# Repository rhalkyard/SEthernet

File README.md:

# SEthernet and SEthernet/30

Modern, low-cost 10/100 Ethernet for the Macintosh SE and SE/30.

## Introduction

It's an unfortunate reality of retrocomputing that, as time goes on, original
hardware only ever becomes more scarce, and usually more expensive.

While PDS ethernet cards are certainly not _scarce_ yet, the collector appeal of
Compact Macs means that cards are in high demand, with consequent high prices.
As of this writing (October 2023), the going eBay rate for them seems to be of
the order of $US 150-200, which is a bit steep for those of us who remember
finding them in electronics-recycler dollar bins.

While other projects have aimed to clone these original cards, such an approach
comes with a downside - the ethernet controller chips used in them have been out
of production for many years, and the controllers and (even more so) their
supporting components, are difficult to find.

While cloned cards trade off parts sourcing difficutly (and cost) for the
significant advantage of being able to use existing drivers, this project takes
the opposite approach: design an all-new card using a modern, readily-available
ethernet controller, and write a new driver for it. How hard can it be?
[^howhard]

## Hardware Overview

Both the SEthernet and SEthernet/30 use the Microchip
[ENC624J600](https://ww1.microchip.com/downloads/aemDocuments/documents/OTH/ProductDocuments/DataSheets/39935c.pdf)
all-in-one embedded ethernet controller. It's cheap, readily available, has a
straightforward software interface without too many glaring misfeatures (I'm
looking at you, RTL8019AS), and amongst its multitude of configurable host-bus
modes, it has one that matches the 68k processor bus nicely.

Since the Macintosh SE lacks any real infrastructure for expansion beyond
"here's a connector with the CPU bus on it," the SEthernet board is a very dumb
device. It simply maps the ENC624J600 into a vacant chunk of memory at `0x80
0000`-`0x80 ffff` and connects it to an interrupt line. Hardware detection,
interrupt vector interception, and device configuration are all left to the
driver to implement.

The Macintosh SE/30 is a more civilised machine, and the SEthernet/30 provides a
[declaration ROM](rom/se30) and multiple addressing options (configurable by
jumper) to take full advantage of the Slot Manager and coexist with multiple PDS
cards. Potentially, the driver could even be built into the declaration ROM,
allowing for a truly plug-and-play solution. To facilitate driver updates, the
declaration ROM is a flash chip, with logic to allow for in-system programming.

## Current project status

### Hardware

Hardware Revision 1 is largely 'done', and corrects the numerous issues of my
initial "Revision 0" boards. A few mechanical tweaks remain to get mounting
holes in exactly the right spot, and relocate connectors for easier access.

### Software

The core driver is functional and stable enough for everyday use. Real-world
performance is marginally better than a comparable vintage card, but there is
likely room to improve - especially in the rather convoluted receive routine.

Support for promiscuous mode, and the `ERead` call are not yet implemented.

The installer has some rough edges (no hardware detection or driver version
detection on the SE), but functions as a way to get drivers onto a system.

The SE/30 board's Declaration ROM must be programmed before the card can be
recognized. This can be done in-system using the
[programROM](software/tools/programROM/) application provided on the installer
disk, but right now this is a very ugly and user-unfriendly console application,
and really should be turned into a proper GUI app.

Testing has been done on my unmodified SE and SE/30 under Systems 6.0.8, 7.1,
and 7.5.5.

A driver for A/UX 2 and 3 can be found at
https://github.com/rhalkyard/SEthernet-AUX. 

## Project files

Schematics: [SEthernet](boards/se/se.pdf) -
[SEthernet/30](boards/se30/se30.pdf) - [Breakout Board](boards/breakout/breakout.pdf)

Glue Logic: [SEthernet](pld/se) - [SEthernet/30](pld/se30)

[SEthernet30 Declaration ROM](rom/se30)

[Driver](software/driver)

## Required tools

### Schematics, board layout and BOM

[KiCad 7](https://www.kicad.org/)

### Programmable Logic

[WinCUPL and ATMISP](https://www.microchip.com/en-us/products/fpgas-and-plds/spld-cplds/pld-design-resources)
(see [`pld/README.md`](pld/README.md) for notes on WinCUPL)

### Declaration ROM, driver and software

- [Retro68](https://github.com/autc04/Retro68) built with [Apple Universal
  Interfaces](https://github.com/autc04/Retro68#apple-universal-interfaces-vs-multiversal-interfaces)
  (at the time of writing, the default free-software Multiversal Interfaces do
  not include some necessary headers)

- [CMake](https://cmake.org/)

- [Python 3](https://www.python.org)

### Installer

- [hfsutils](https://www.mars.org/home/rob/proj/hfs/)

- [Python 3](https://www.python.org)

- [Mini vMac](https://www.gryphel.com/c/minivmac/index.html)

## License

The hardware components of this project ([board designs](boards/) and
[programmable logic](pld/)) are licensed under the [Strongly-Reciprocal CERN
Open Hardware License, version 2](CERN-OHL-S-2.0).

The [software components](software/) of this project are licensed under the [GNU
General Public License v3.0](COPYING).

While my choice to make this project open-source is very much a deliberate one,
I have a few further requests, on the basis of "I can't and won't enforce these,
but I'd appreciate if you respected them." It's unfortunate that I have to
mention this, but given how a few recent projects in the retro-hardware
community have splintered, I feel that it's necessary to say:

- Please don't sell cards commercially/for profit without checking with me
  first. I have plans for a sales and manufacturing partnership that will sell
  boards affordably, with full support. I don't mind if you order a batch of
  boards for yourself and sell the extras on a break-even basis, but please make
  it clear that these are not 'official' SEthernet products.

- Please contribute back, rather than simply forking the project. I strongly
  encourage people to modify the design, adapt it to other systems, integrate it
  into other devices. But unless what you're working on is a radical departure
  from the basic SEthernet design, I'd much rather see a unified, collaborative
  effort that is supported by a single software stack, rather than having it be
  fragmented.

If you have any questions, feel free to reach out to me, I don't bite!

## Useful reference material

- [ENC624J600 datasheet](https://ww1.microchip.com/downloads/aemDocuments/documents/OTH/ProductDocuments/DataSheets/39935c.pdf)

- [Designing Cards and Drivers for the Macintosh Family (3rd
  Edition)](https://www.vintageapple.org/inside_o/pdf/Designing_Cards_and_Drivers_for_the_Macintosh_Family_3rd_Edition_1992.pdf)

- [Inside Macintosh (1994): Networking](https://www.vintageapple.org/inside_r/pdf/Networking_1994.pdf)

- [Inside Macintosh (1994): Devices](https://www.vintageapple.org/inside_r/pdf/Devices_1994.pdf)

- [Glenn Anderson's ethernet driver page](https://www.mactcp.net/ethernet.html) -
  contains C source for a DP8390-based card.

- [Mac Driver Museum: Network
  Drivers](https://vintageapple.org/macdrivers/network.shtml) - good material
  for reverse-engineering. In particular, the Dayna ethernet drivers contain
  debug symbols, which are quite handy for our purposes.

- [Rob Braun's declaration ROM page](http://www.synack.net/~bbraun/declrom.html)
  has useful information about declaration ROMs and how they work.

[^howhard]: [Arrested Development narrator voice]: It was, in fact, quite hard

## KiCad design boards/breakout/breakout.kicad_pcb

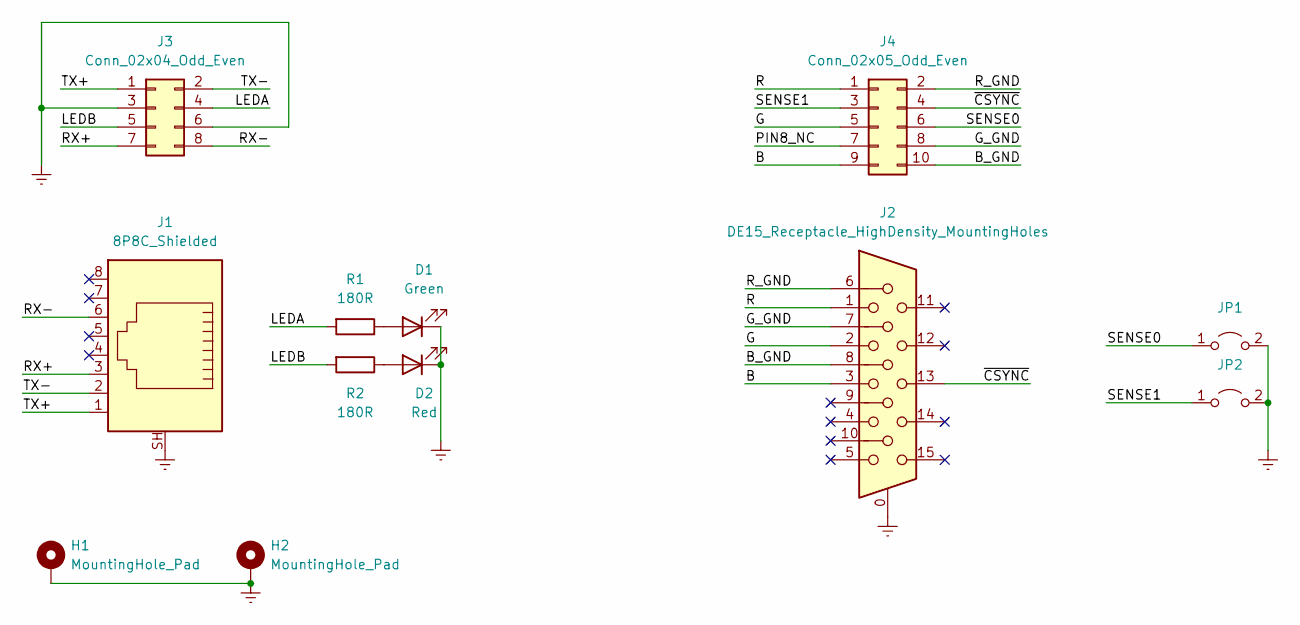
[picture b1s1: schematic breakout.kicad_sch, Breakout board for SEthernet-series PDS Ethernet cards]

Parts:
D1: Green; LED_D3.0mm; Digikey 151031VS06000
D2: Red; LED_D3.0mm; Digikey 151031SS06000
H1, H2: MountingHole_Pad; Wurth_9774025360R; Digikey 9774025360R
J1: 8P8C_Shielded; Kycon-GDTX-S-88_Vertical; Digikey GDTX-S-88
J2: DE15_Receptacle_HighDensity_MountingHoles; DSUB-15-HD_Female_Vertical_P2.29x1.98mm_MountingHoles; Digikey L77HDEH15SOL2RM832
J3: Conn_02x04_Odd_Even; IDC-Header_2x04_P2.54mm_Vertical; Digikey 302-S101
J4: Conn_02x05_Odd_Even; IDC-Header_2x05_P2.54mm_Vertical; Digikey 302-S101
JP1, JP2: Jumper_2_Bridged; PinHeader_1x02_P2.54mm_Vertical
R1, R2: 180R; R_Axial_DIN0204_L3.6mm_D1.6mm_P7.62mm_Horizontal; Digikey CF18JT180R

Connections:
/B: J2.3, J4.9
/B_GND: J2.8, J4.10
/G: J2.2, J4.5
/G_GND: J2.7, J4.8
/LEDA: J3.4, R1.2
/LEDB: J3.5, R2.2
/PIN8_NC: J4.7
/R: J2.1, J4.1
/RX+: J1.3, J3.7
/RX-: J1.6, J3.8
/R_GND: J2.6, J4.2
/SENSE0: J4.6, JP1.1 (A)
/SENSE1: J4.3, JP2.1 (A)
/TX+: J1.1, J3.1
/TX-: J1.2, J3.2
/~CSYNC: J2.13, J4.4
Earth: D1.1 (K), D2.1 (K), H1.1, H2.1, J1.SH, J2.0, J3.3, J3.6, JP1.2 (B), JP2.2 (B)
unnamed: D1.2 (A), R1.1
unnamed: D2.2 (A), R2.1

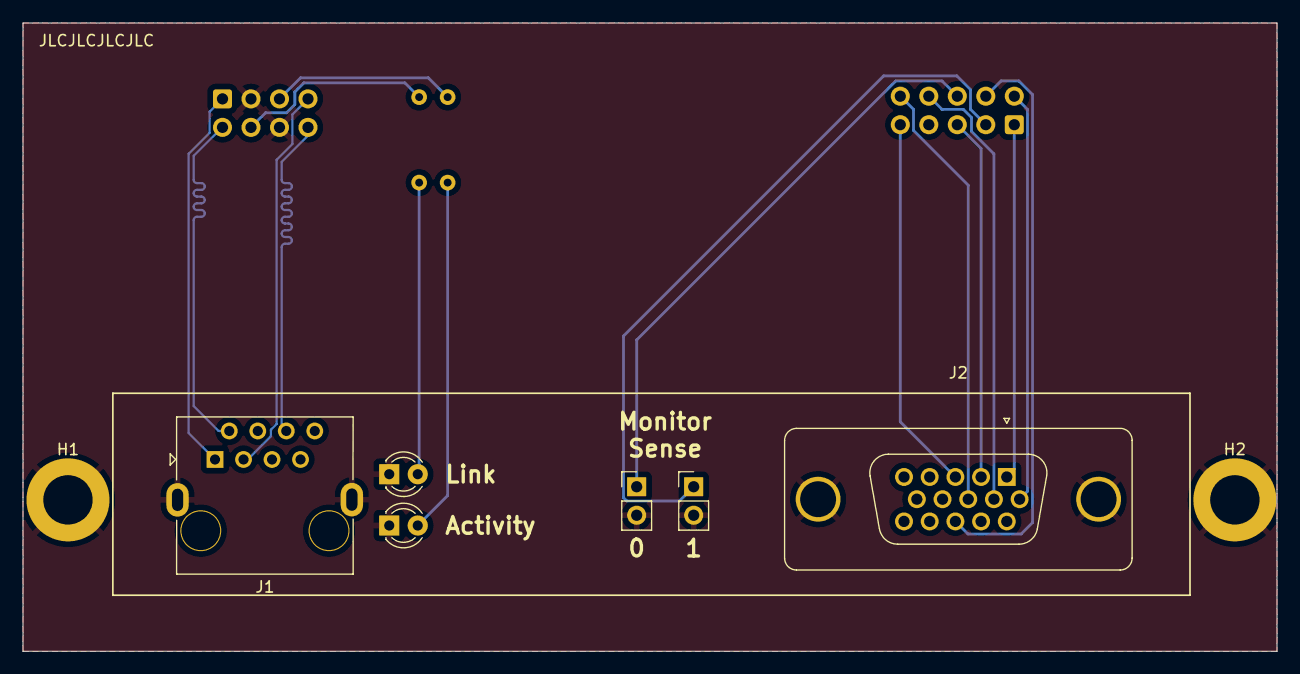
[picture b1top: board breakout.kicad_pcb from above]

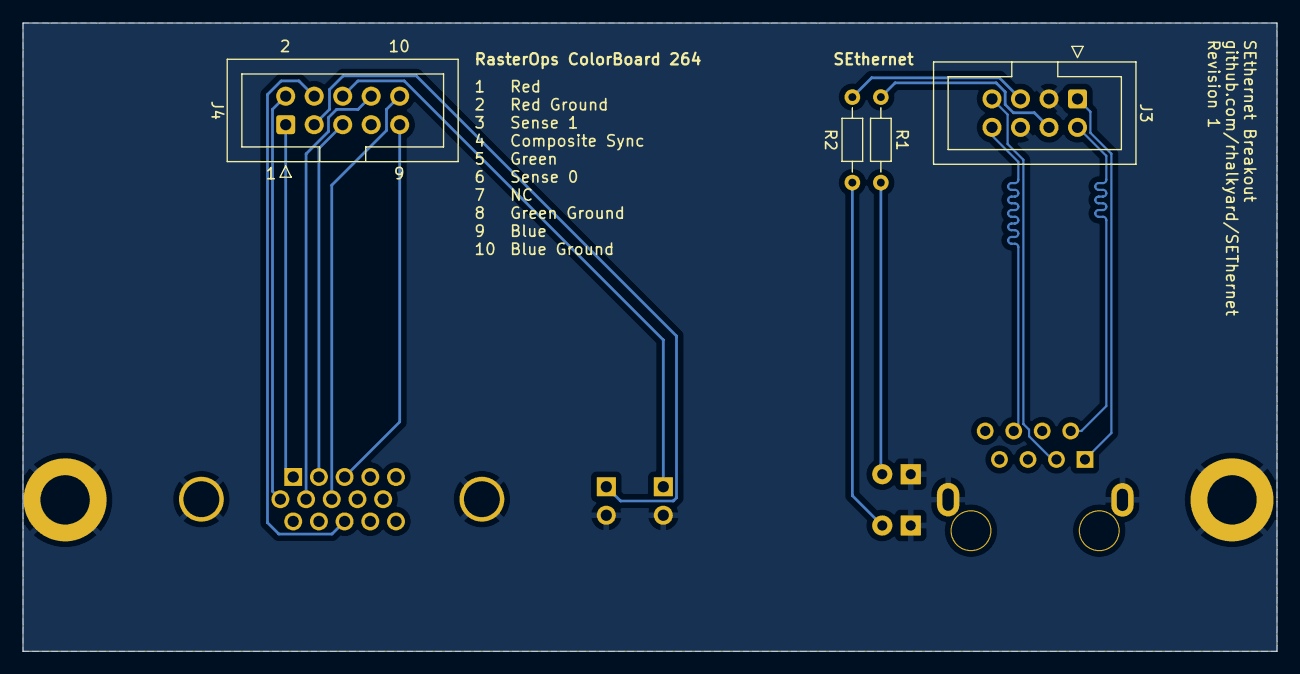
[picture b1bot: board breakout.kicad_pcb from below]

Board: 2 copper layers, 111.8 x 56.0 mm, 12 parts (4 on the bottom side), 18 nets.

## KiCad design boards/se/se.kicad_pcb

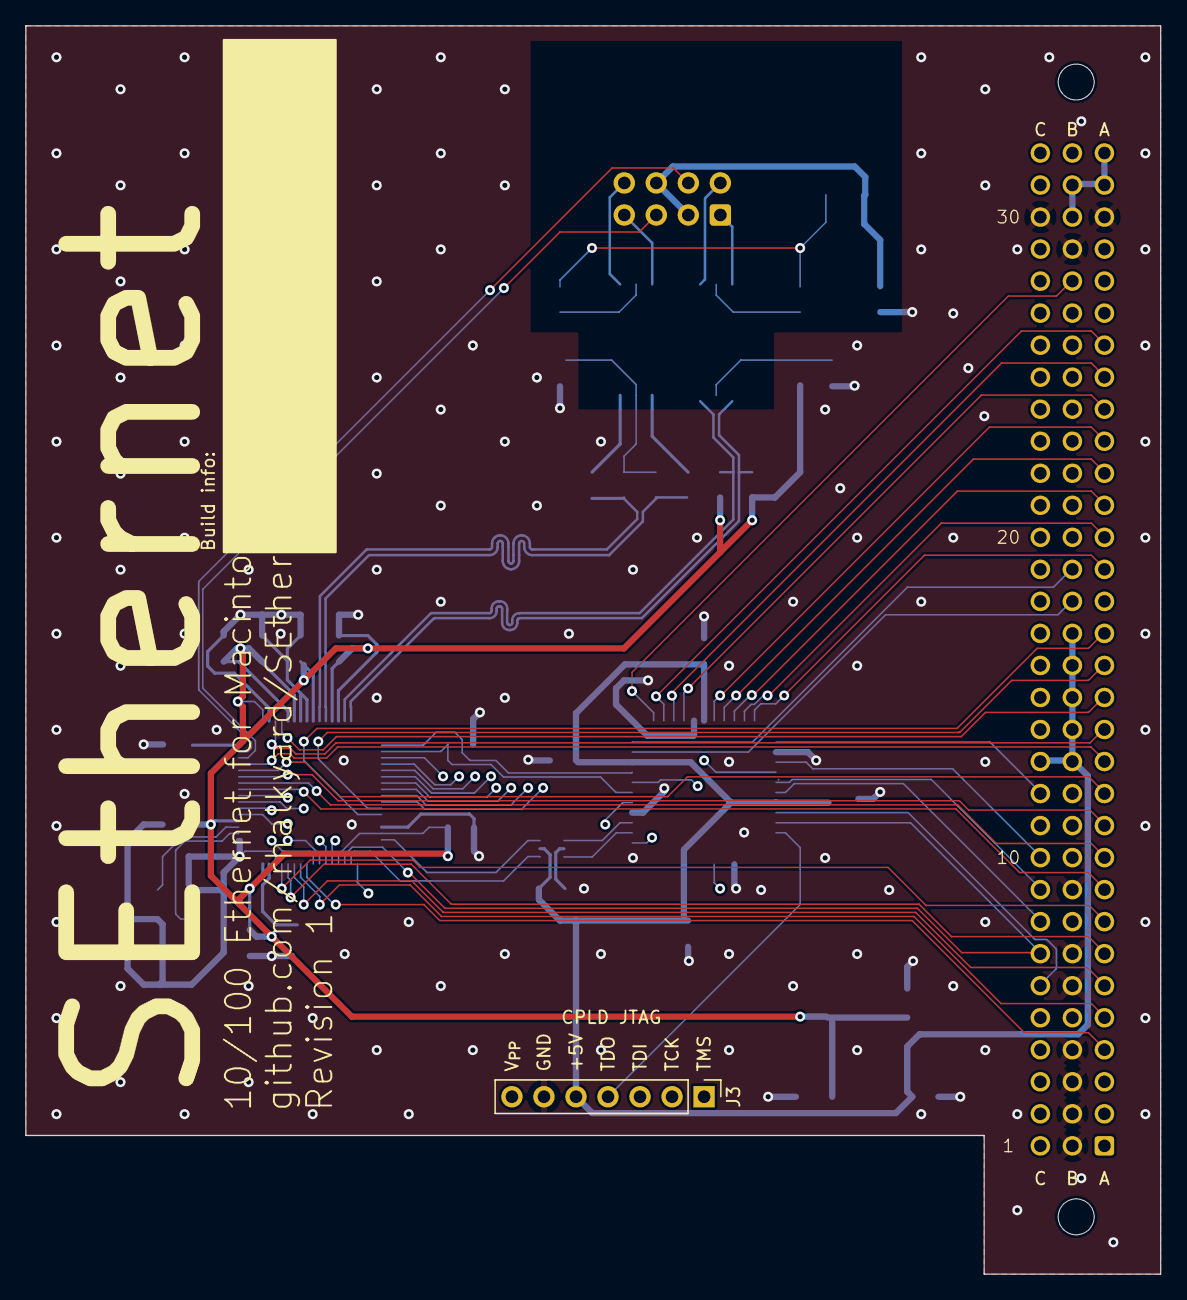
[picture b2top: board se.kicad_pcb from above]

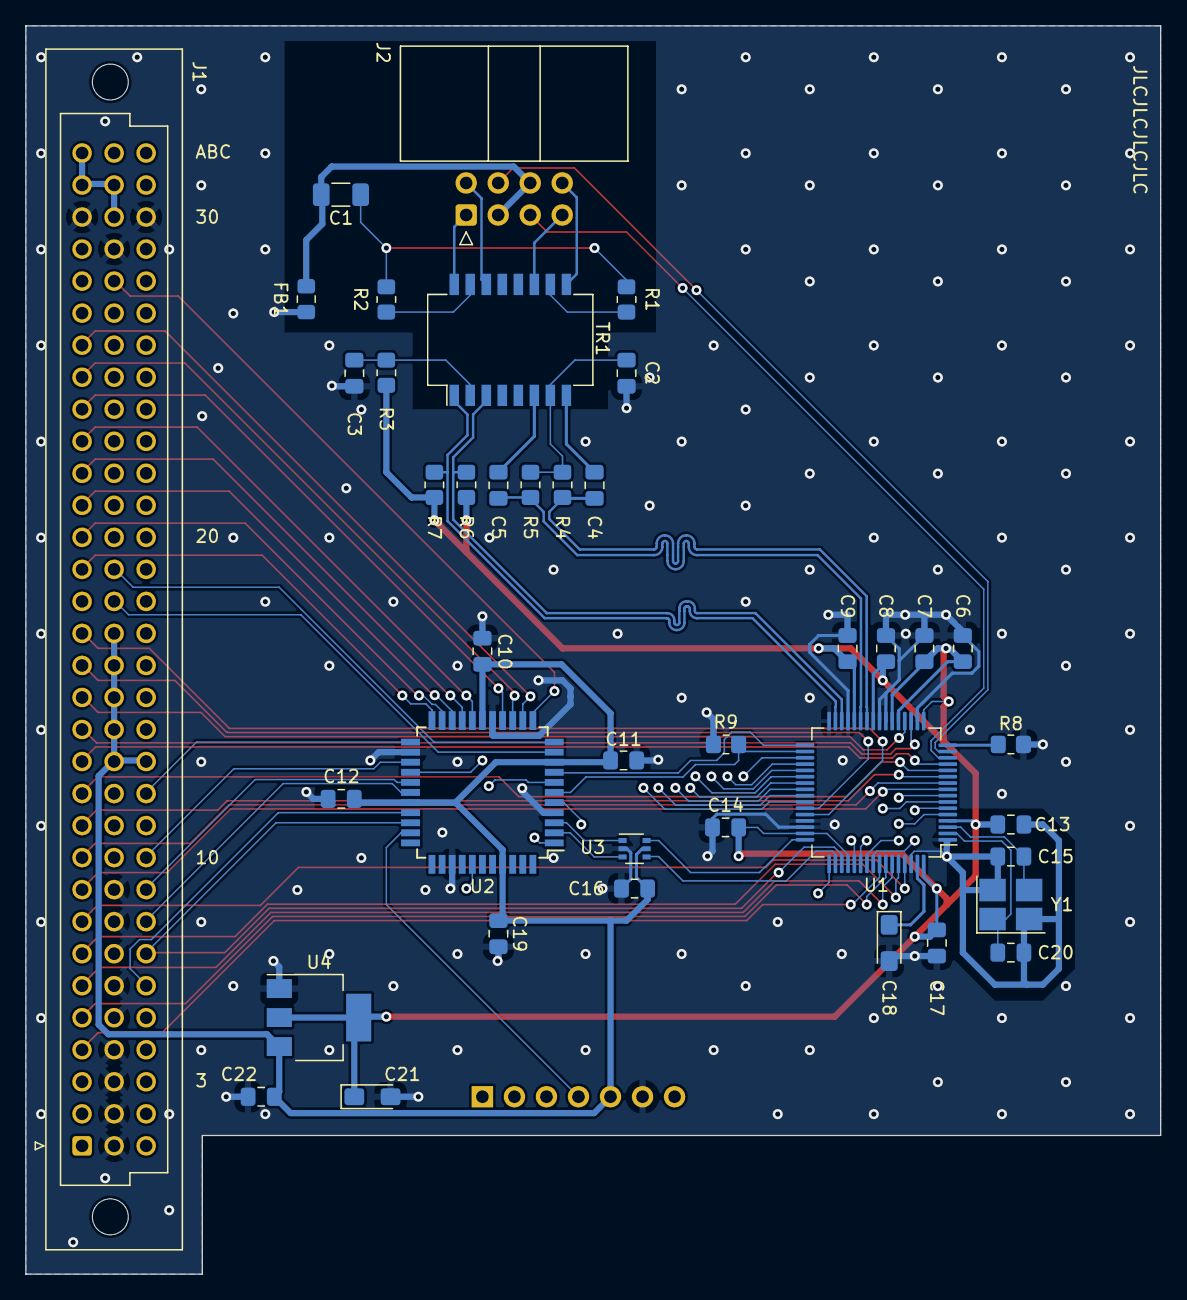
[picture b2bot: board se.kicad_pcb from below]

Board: 4 copper layers, 90.0 x 99.0 mm, 41 parts (40 on the bottom side), 85 nets.

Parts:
C1: 1000pF 2KV; C_1206_3216Metric_Pad1.33x1.80mm_HandSolder
C2, C3: 0.01uF; C_0805_2012Metric_Pad1.18x1.45mm_HandSolder
C4, C5: 6.8nF; C_0805_2012Metric_Pad1.18x1.45mm_HandSolder
C6, C10, C11, C12, C14, C16, C17, C19: 1uF; C_0805_2012Metric_Pad1.18x1.45mm_HandSolder
C7, C8, C9, C13, C22: 0.1uF; C_0805_2012Metric_Pad1.18x1.45mm_HandSolder
C15, C20: 18pF; C_0805_2012Metric_Pad1.18x1.45mm_HandSolder
C18, C21: 10uF; CP_EIA-3216-18_Kemet-A_Pad1.58x1.35mm_HandSolder
FB1: FerriteBead; L_0805_2012Metric_Pad1.15x1.40mm_HandSolder
J1: Macintosh SE PDS Interface; DIN41612_C_3x32_Female_Vertical_THT_Reversed
J2: Conn_02x05_Odd_Even; IDC-Header_2x04_P2.54mm_Horizontal
J3: Conn_01x07; PinHeader_1x07_P2.54mm_Vertical
R1, R2: 75; R_0805_2012Metric_Pad1.20x1.40mm_HandSolder
R3: 10R 1/12W; R_0805_2012Metric_Pad1.20x1.40mm_HandSolder
R4, R5, R6, R7: 49.9; R_0805_2012Metric_Pad1.20x1.40mm_HandSolder
R8: 12.4K; R_0805_2012Metric_Pad1.20x1.40mm_HandSolder
R9: 100K; R_0805_2012Metric_Pad1.20x1.40mm_HandSolder
TR1: PT61017PEL; Transformer_Ethernet_Bourns_PT61017PEL
U1: ENC624J600-PT; TQFP-64_10x10mm_P0.5mm
U2: ATF1502AS-xAx44; TQFP-44_10x10mm_P0.8mm
U3: 74LVC2G17; SOT-363_SC-70-6
U4: LD1117S33TR_SOT223; SOT-223-3_TabPin2
Y1: 25MHz; Crystal_SMD_3225-4Pin_3.2x2.5mm_HandSoldering

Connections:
+3.3V: C6.1, C7.1, C8.2, C9.1, C13.2, C14.1, C17.2, C21.1, R3.1, R6.1, R7.2, U1.4 (VDDOSC), U1.17 (PSPCFG2), U1.21 (VDD), U1.22 (VDDPLL), U1.25 (VDDRX), U1.28 (VDDTX), U1.47 (VDD), U1.52 (AL/PSPCFG4/SCK), U1.64 (VDD), U4.2 (VO)
+5V: C10.1, C11.1, C12.1, C16.1, C19.1, C22.1, J1.b13 (+5V), J1.b14 (+5V), J1.b15 (+5V), J1.b16 (+5V), J1.b17 (+5V), J1.c13 (+5V), J3.5, U2.9 (VCC), U2.17 (VCC), U2.29 (VCC), U2.41 (VCC), U3.5 (VCC), U4.3 (VI)
+12V: J1.a31 (+12V), J1.a32 (+12V), J1.b30 (+12V), J1.b31 (+12V)
/B0SEL: U2.2 (I/O), U3.3
/B0SEL': U1.50 (WR/WRL/B0SEL/SO), U3.4
/B1SEL: U2.3 (I/O), U3.1
/B1SEL': U1.48 (WRH/B1SEL), U3.6
/CPLD_VPP: J3.7, U2.38 (I/OE1/Vpp)
/ETH_CLK: U1.33 (CLKOUT), U2.8 (I/O)
/ETH_CS: U1.49 (~CS/CS), U2.5 (I/O/PD1)
/ETH_~INT: R9.2, U1.34 (~INT/SPISEL), U2.6 (I/O)
/LEDA: J2.4, U1.15 (LEDA)
/LEDB: J2.5, U1.14 (LEDB)
/RX+: J2.7, TR1.11 (RX+)
/RX-: J2.8, TR1.9 (RX-)
/TCK: J3.2, U2.26 (I/O/TCK)
/TDI: J3.3, U2.1 (I/O/TDI)
/TDO: J3.4, U2.32 (I/O/TDO)
/TMS: J3.1, U2.7 (I/O/TMS)
/TPIN'+: C5.2, TR1.6 (RD+)
/TPIN'-: C4.2, TR1.8 (RD-)
/TPIN+: C5.1, R5.1, U1.27 (TPIN+)
/TPIN-: C4.1, R4.2, U1.26 (TPIN-)
/TPOUT+: R7.1, TR1.1 (TD+), U1.31 (TPOUT+)
/TPOUT-: R6.2, TR1.3 (TD-), U1.30 (TPOUT-)
/TX+: J2.1, TR1.16 (TX+)
/TX-: J2.2, TR1.14 (TX-)
A1: J1.a4 (A1), U1.57 (A0)
A2: J1.a5 (A2), U1.58 (A1)
A3: J1.a6 (A3), U1.59 (A2)
A4: J1.a7 (A4), U1.60 (A3)
A5: J1.a8 (A5), U1.61 (A4)
A6: J1.a9 (A6), U1.9 (A5)
A7: J1.a10 (A7), U1.10 (A6)
A8: J1.a11 (A8), U1.11 (A7)
A9: J1.a12 (A9), U1.12 (A8)
A10: J1.a13 (A10), U1.13 (A9)
A11: J1.a14 (A11), U1.19 (A10)
A12: J1.a15 (A12), U1.20 (A11)
A13: J1.a16 (A13), U1.43 (A12)
A14: J1.a17 (A14), U1.44 (A13)
A16: J1.a19 (A16), U2.22 (I/O)
A17: J1.a20 (A17), U2.21 (I/O)
A18: J1.a21 (A18), U2.20 (I/O)
A19: J1.a22 (A19), U2.19 (I/O/PD2)
A20: J1.a23 (A20), U2.18 (I/O)
A21: J1.a24 (A21), U2.15 (I/O)
A22: J1.a25 (A22), U2.14 (I/O)
A23: J1.a26 (A23), U2.13 (I/O)
D0: J1.c14 (D0), U1.35 (AD8)
D1: J1.c15 (D1), U1.36 (AD9)
D2: J1.c16 (D2), U1.37 (AD10)
D3: J1.c17 (D3), U1.38 (AD11)
D4: J1.c18 (D4), U1.39 (AD12)
D5: J1.c19 (D5), U1.40 (AD13)
D6: J1.c20 (D6), U1.41 (AD14)
D7: J1.c21 (D7), U1.42 (AD15)
D8: J1.c22 (D8), U1.53 (AD0)
D9: J1.c23 (D9), U1.54 (AD1)
D10: J1.c24 (D10), U1.55 (AD2)
D11: J1.c25 (D11), U1.56 (AD3)
D12: J1.c26 (D12), U1.5 (AD4)
D13: J1.c27 (D13), U1.6 (AD5)
D14: J1.c28 (D14), U1.7 (AD6)
D15: J1.c29 (D15), U1.8 (AD7)
Earth: C1.2, FB1.2, J2.3, J2.6
GND: C2.2, C3.2, C6.2, C7.2, C8.1, C9.2, C10.2, C11.2, C12.2, C13.1, C14.2, C15.2, C16.2, C17.1, C18.2, C19.2, C20.2, C21.2, C22.2, FB1.1, J1.a30 (GND), J1.b1 (GND), J1.b2 (GND), J1.b3 (GND), J1.b4 (GND), J1.b5 (GND), J1.b6 (GND), J1.b7 (GND), J1.b8 (GND), J1.b9 (GND), J1.b29 (GND), J1.c30 (GND), J3.6, R8.2, R9.1, U1.1 (VSSOSC), U1.18 (PSPCFG3), U1.23 (VSSPLL), U1.24 (VSSRX), U1.29 (VSSTX), U1.32 (VSSTX), U1.45 (A14/PSPCFG1), U1.46 (VSS), U1.62 (VSS), U2.4 (GND), U2.16 (GND), U2.24 (GND), U2.36 (GND), U3.2 (GND), U4.1 (GND), Y1.2, Y1.4
unnamed: C1.1, R1.2, R2.2
unnamed: C2.1, R4.1, R5.2, TR1.7 (C_RD)
unnamed: R1.1, TR1.10 (C_RX)
unnamed: C3.1, R3.2, TR1.2 (C_TD)
unnamed: R2.1, TR1.15 (C_TX)
unnamed: C15.1, U1.3 (OSC1), Y1.3
unnamed: C20.1, U1.2 (OSC2), Y1.1
unnamed: R8.1, U1.16 (RBIAS)
unnamed: C18.1, U1.63 (VCAP)
R/~W: J1.c7 (R/~W), U1.51 (SI/RD/R~W), U2.31 (I/O)
~AS: J1.c10 (~AS), U2.25 (I/O)
~DTACK: J1.c6 (~DTACK), U2.30 (I/O)
~EXT_DTK: J1.b28 (~EXT_DTK), U2.12 (I/O)
~IPL0: J1.b18 (~IPL0), U2.10 (I/O)
~IPL1: J1.b19 (~IPL1), U2.11 (I/O)
~LDS: J1.c8 (~LDS), U2.28 (I/O)
~RESET: J1.c12 (~RESET), U2.23 (I/O)
~UDS: J1.c9 (~UDS), U2.27 (I/O)

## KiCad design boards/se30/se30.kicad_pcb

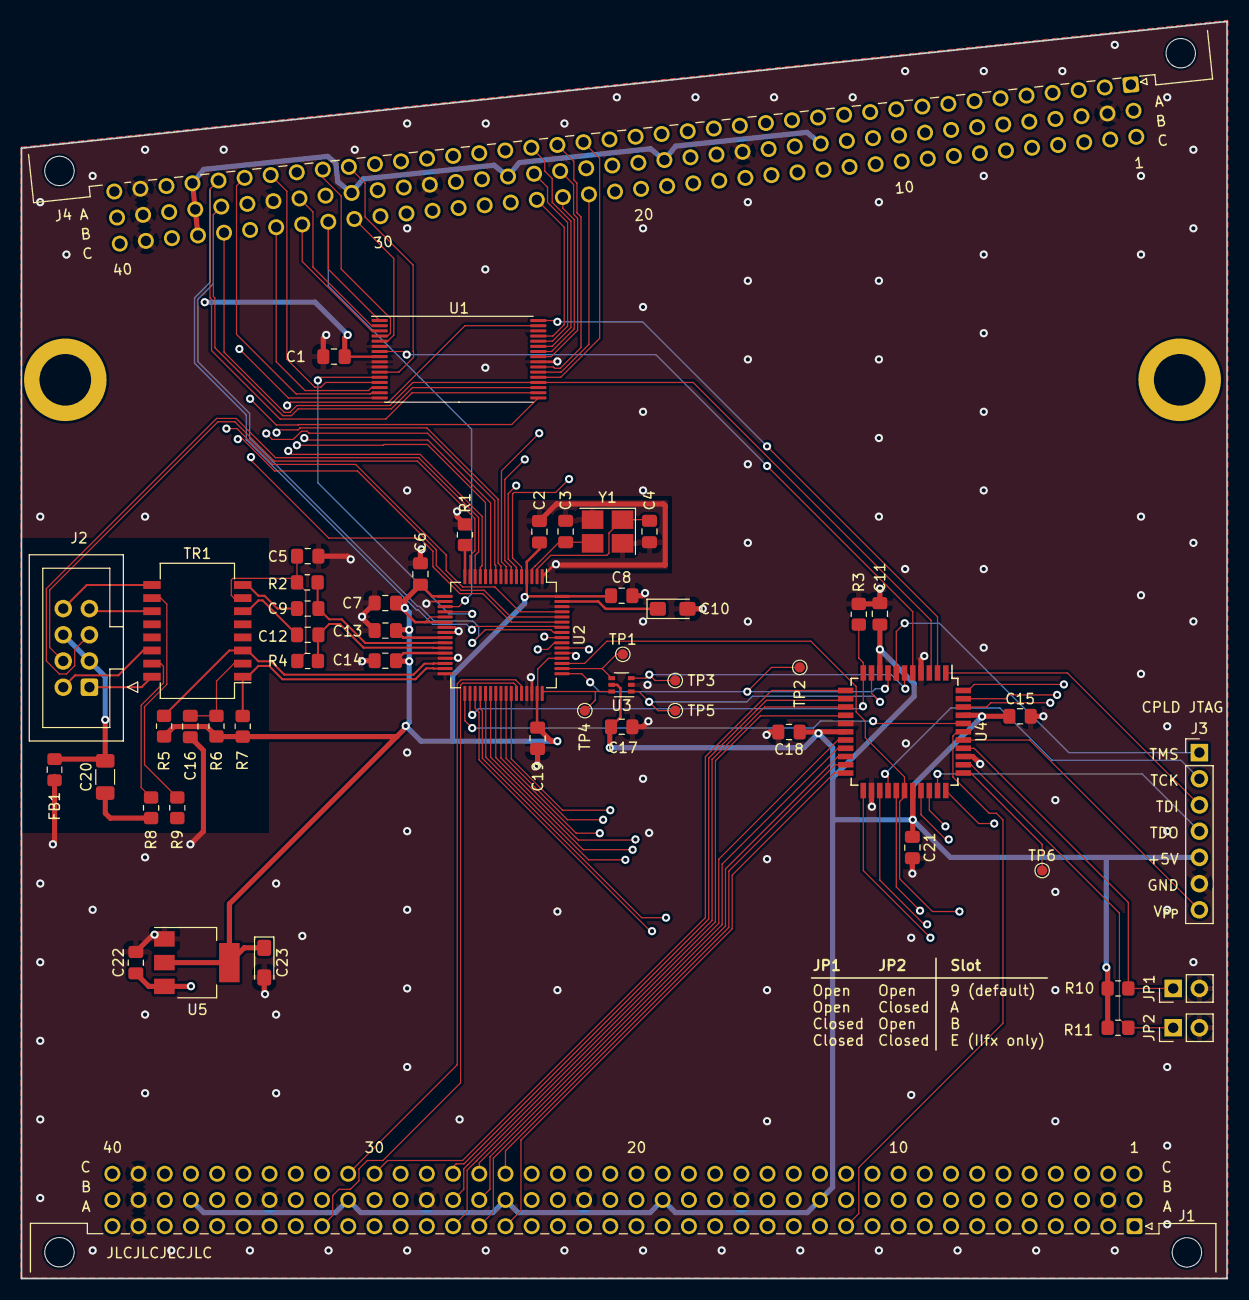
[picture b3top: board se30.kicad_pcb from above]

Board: 4 copper layers, 116.8 x 121.8 mm, 56 parts (0 on the bottom side), 147 nets.

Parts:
C1, C6, C8, C11, C15, C17, C18, C19, C21: 1uF; C_0805_2012Metric_Pad1.18x1.45mm_HandSolder
C2, C7, C13, C14, C22: 0.1uF; C_0805_2012Metric_Pad1.18x1.45mm_HandSolder
C3, C4: 18pF; C_0805_2012Metric_Pad1.18x1.45mm_HandSolder
C5, C16: 0.01uF; C_0805_2012Metric_Pad1.18x1.45mm_HandSolder
C9, C12: 6.8nF; C_0805_2012Metric_Pad1.18x1.45mm_HandSolder
C10, C23: 10uF; CP_EIA-3216-18_Kemet-A_Pad1.58x1.35mm_HandSolder
C20: 1000pF 2KV; C_1206_3216Metric_Pad1.33x1.80mm_HandSolder
FB1: FerriteBead; L_0805_2012Metric_Pad1.15x1.40mm_HandSolder
H1, H2: MountingHole; MountingHole_5mm
J1: Mac SE/30 PDS Interface; DIN41612_C_3x40_Male_Horizontal_THT
J2: Conn_02x05_Odd_Even; IDC-Header_2x04_P2.54mm_Vertical
J3: Conn_01x07; PinHeader_1x07_P2.54mm_Vertical
J4: Mac SE/30 PDS Interface; DIN41612_C_3x40_Female_Horizontal_THT
JP1, JP2: SolderJumper_2_Open; PinHeader_1x02_P2.54mm_Vertical
R1: 12.4K; R_0805_2012Metric_Pad1.20x1.40mm_HandSolder
R2, R4, R5, R7: 49.9; R_0805_2012Metric_Pad1.20x1.40mm_HandSolder
R3: 100K; R_0805_2012Metric_Pad1.20x1.40mm_HandSolder
R6: 10R 1/12W; R_0805_2012Metric_Pad1.20x1.40mm_HandSolder
R8, R9: 75; R_0805_2012Metric_Pad1.20x1.40mm_HandSolder
R10, R11: 10K; R_0805_2012Metric_Pad1.20x1.40mm_HandSolder
TP1, TP2, TP3, TP4, TP5, TP6: TestPoint; TestPoint_Pad_D1.0mm
TR1: PT61017PEL; Transformer_Ethernet_Bourns_PT61017PEL
U1: SST39SF010; TSOP-I-32_14.4x8mm_P0.5mm
U2: ENC624J600-PT; TQFP-64_10x10mm_P0.5mm
U3: 74LVC2G17; SOT-363_SC-70-6
U4: ATF1502AS-xAx44; TQFP-44_10x10mm_P0.8mm
U5: LD1117S33TR_SOT223; SOT-223-3_TabPin2
Y1: 25MHz; Crystal_SMD_3225-4Pin_3.2x2.5mm_HandSoldering

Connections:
+3.3V: C2.2, C6.2, C7.1, C8.1, C13.2, C14.1, C19.1, C23.1, R5.1, R6.1, R7.2, U2.4 (VDDOSC), U2.17 (PSPCFG2), U2.21 (VDD), U2.22 (VDDPLL), U2.25 (VDDRX), U2.28 (VDDTX), U2.47 (VDD), U2.52 (AL/PSPCFG4/SCK), U2.64 (VDD), U5.2 (VO)
+5V: C1.1, C11.1, C15.1, C17.1, C18.1, C21.1, C22.1, J1.a37 (+5V), J1.b13 (+5V), J1.b19 (+5V), J1.b25 (+5V), J1.b31 (+5V), J1.b37 (+5V), J1.c37 (+5V), J3.5, J4.a37 (+5V), J4.b13 (+5V), J4.b19 (+5V), J4.b25 (+5V), J4.b31 (+5V), J4.b37 (+5V), J4.c37 (+5V), R10.1, R11.1, U1.8 (VCC), U3.5 (VCC), U4.9 (VCC), U4.17 (VCC), U4.29 (VCC), U4.41 (VCC), U5.3 (VI)
+12V: J1.c40 (+12V), J4.c40 (+12V)
-5V: J1.b40 (-5V), J4.b40 (-5V)
-12V: J1.a40 (-12V), J4.a40 (-12V)
/B0SEL: TP3.1, U3.3, U4.6 (I/O)
/B0SEL': TP1.1, U2.50 (WR/WRL/B0SEL/SO), U3.4
/B1SEL: TP5.1, U3.1, U4.10 (I/O)
/B1SEL': TP4.1, U2.48 (WRH/B1SEL), U3.6
/CPLD_VPP: J3.7, U4.38 (I/OE1/Vpp)
/ENC_CLK: U2.33 (CLKOUT), U4.40 (I/OE2/GCLK2)
/ETH_CS: TP2.1, U2.49 (~CS/CS), U4.8 (I/O)
/ETH_~INT: R3.2, U2.34 (~INT/SPISEL), U4.11 (I/O)
/LEDA: J2.4, U2.15 (LEDA)
/LEDB: J2.5, U2.14 (LEDB)
/PDS Interface/C16M: J1.c38 (C16M), J4.c38 (C16M)
/PDS Interface/ECLK: J1.b38 (ECLK), J4.b38 (ECLK)
/PDS Interface/FC0: J1.c11 (FC0), J4.c11 (FC0)
/PDS Interface/FC1: J1.b11 (FC1), J4.b11 (FC1)
/PDS Interface/FC2: J1.a11 (FC2), J4.a11 (FC2)
/PDS Interface/PFW: J1.c1 (PFW), J4.c1 (PFW)
/PDS Interface/RESV_A1: J1.a1 (Reserved), J4.a1 (Reserved)
/PDS Interface/RESV_A2: J1.a2 (Reserved), J4.a2 (Reserved)
/PDS Interface/RESV_B1: J1.b1 (Reserved), J4.b1 (Reserved)
/PDS Interface/~BERR: J1.b12 (~BERR), J4.b12 (~BERR)
/PDS Interface/~BGACK: J1.a10 (~BGACK), J4.a10 (~BGACK)
/PDS Interface/~BG: J1.b10 (~BG), J4.b10 (~BG)
/PDS Interface/~BR: J1.c10 (~BR), J4.c10 (~BR)
/PDS Interface/~BUSLOCK: J1.a3 (~BUSLOCK), J4.a3 (~BUSLOCK)
/PDS Interface/~CBACK: J1.b7 (~CBACK), J4.b7 (~CBACK)
/PDS Interface/~CBREQ: J1.c7 (~CBREQ), J4.c7 (~CBREQ)
/PDS Interface/~CIOUT: J1.a6 (~CIOUT), J4.a6 (~CIOUT)
/PDS Interface/~HALT: J1.c12 (~HALT), J4.c12 (~HALT)
/PDS Interface/~IPL0: J1.c5 (~IPL0), J4.c5 (~IPL0)
/PDS Interface/~IPL1: J1.b5 (~IPL1), J4.b5 (~IPL1)
/PDS Interface/~IPL2: J1.a5 (~IPL2), J4.a5 (~IPL2)
/PDS Interface/~RMC: J1.c6 (~RMC), J4.c6 (~RMC)
/PDS Interface/~STERM: J1.a7 (~STERM), J4.a7 (~STERM)
/PDS Interface/~TM0A: J1.c3 (~TM0A), J4.c3 (~TM0A)
/PDS Interface/~TM1A: J1.b3 (~TM1A), J4.b3 (~TM1A)
/ROM_~OE: U1.32 (OE), U4.2 (I/O)
/ROM_~WE: U1.7 (PGM), U4.5 (I/O/PD1)
/RX+: J2.7, TR1.11 (RX+)
/RX-: J2.8, TR1.9 (RX-)
/TCK: J3.2, U4.26 (I/O/TCK)
/TDI: J3.3, U4.1 (I/O/TDI)
/TDO: J3.4, U4.32 (I/O/TDO)
/TMS: J3.1, U4.7 (I/O/TMS)
/TPIN'+: C12.2, TR1.6 (RD+)
/TPIN'-: C9.2, TR1.8 (RD-)
/TPIN+: C12.1, R4.1, U2.27 (TPIN+)
/TPIN-: C9.1, R2.2, U2.26 (TPIN-)
/TPOUT+: R7.1, TR1.1 (TD+), U2.31 (TPOUT+)
/TPOUT-: R5.2, TR1.3 (TD-), U2.30 (TPOUT-)
/TX+: J2.1, TR1.16 (TX+)
/TX-: J2.2, TR1.14 (TX-)
/~SLOTID_0: JP2.1 (A), R11.2, U4.35 (I/O/GCLK3)
/~SLOTID_1: JP1.1 (A), R10.2, U4.37 (I/GCLK1)
A0: J1.c36 (A0), J4.c36 (A0), U1.20 (A0), U4.3 (I/O)
A1: J1.b36 (A1), J4.b36 (A1), U1.19 (A1), U2.57 (A0)
A2: J1.a36 (A2), J4.a36 (A2), U1.18 (A2), U2.58 (A1)
A3: J1.c35 (A3), J4.c35 (A3), U1.17 (A3), U2.59 (A2)
A4: J1.b35 (A4), J4.b35 (A4), U1.16 (A4), U2.60 (A3)
A5: J1.a35 (A5), J4.a35 (A5), U1.15 (A5), U2.61 (A4)
A6: J1.c34 (A6), J4.c34 (A6), U1.14 (A6), U2.9 (A5)
A7: J1.a34 (A7), J4.a34 (A7), U1.13 (A7), U2.10 (A6)
A8: J1.c33 (A8), J4.c33 (A8), U1.3 (A8), U2.11 (A7)
A9: J1.b33 (A9), J4.b33 (A9), U1.2 (A9), U2.12 (A8)
A10: J1.a33 (A10), J4.a33 (A10), U1.31 (A10), U2.13 (A9)
A11: J1.c32 (A11), J4.c32 (A11), U1.1 (A11), U2.19 (A10)
A12: J1.b32 (A12), J4.b32 (A12), U1.12 (A12), U2.20 (A11)
A13: J1.a32 (A13), J4.a32 (A13), U1.4 (A13), U2.43 (A12)
A14: J1.c31 (A14), J4.c31 (A14), U1.5 (A14), U2.44 (A13)
A15: J1.a31 (A15), J4.a31 (A15), U1.11 (A15)
A16: J1.c30 (A16), J4.c30 (A16), U4.12 (I/O)
A17: J1.b30 (A17), J4.b30 (A17)
A18: J1.a30 (A18), J4.a30 (A18)
A19: J1.c29 (A19), J4.c29 (A19)
A20: J1.b29 (A20), J4.b29 (A20)
A21: J1.a29 (A21), J4.a29 (A21)
A22: J1.c28 (A22), J4.c28 (A22)
A23: J1.a28 (A23), J4.a28 (A23)
A24: J1.c27 (A24), J4.c27 (A24), U4.13 (I/O)
A25: J1.b27 (A25), J4.b27 (A25), U4.14 (I/O)
A26: J1.a27 (A26), J4.a27 (A26), U4.15 (I/O)
A27: J1.c26 (A27), J4.c26 (A27), U4.18 (I/O)
A28: J1.b26 (A28), J4.b26 (A28), U4.19 (I/O/PD2)
A29: J1.a26 (A29), J4.a26 (A29), U4.20 (I/O)
A30: J1.c25 (A30), J4.c25 (A30), U4.21 (I/O)
A31: J1.a25 (A31), J4.a25 (A31), U4.22 (I/O)
CPUCLK: J1.a38 (CPUCLK), J4.a38 (CPUCLK)
D0: J1.a13 (D0), J4.a13 (D0)
D1: J1.c13 (D1), J4.c13 (D1)
D2: J1.a14 (D2), J4.a14 (D2)
D3: J1.b14 (D3), J4.b14 (D3)
D4: J1.c14 (D4), J4.c14 (D4)
D5: J1.a15 (D5), J4.a15 (D5)
D6: J1.b15 (D6), J4.b15 (D6)
D7: J1.c15 (D7), J4.c15 (D7)
D8: J1.a16 (D8), J4.a16 (D8)
D9: J1.c16 (D9), J4.c16 (D9)
D10: J1.a17 (D10), J4.a17 (D10)
D11: J1.b17 (D11), J4.b17 (D11)
D12: J1.c17 (D12), J4.c17 (D12)
D13: J1.a18 (D13), J4.a18 (D13)
D14: J1.b18 (D14), J4.b18 (D14)
D15: J1.c18 (D15), J4.c18 (D15)
D16: J1.a19 (D16), J4.a19 (D16), U2.35 (AD8)
D17: J1.c19 (D17), J4.c19 (D17), U2.36 (AD9)
D18: J1.a20 (D18), J4.a20 (D18), U2.37 (AD10)
D19: J1.b20 (D19), J4.b20 (D19), U2.38 (AD11)
D20: J1.c20 (D20), J4.c20 (D20), U2.39 (AD12)
D21: J1.a21 (D21), J4.a21 (D21), U2.40 (AD13)
D22: J1.b21 (D22), J4.b21 (D22), U2.41 (AD14)
D23: J1.c21 (D23), J4.c21 (D23), U2.42 (AD15)
D24: J1.a22 (D24), J4.a22 (D24), U1.21 (D0), U2.53 (AD0)
D25: J1.c22 (D25), J4.c22 (D25), U1.22 (D1), U2.54 (AD1)
D26: J1.a23 (D26), J4.a23 (D26), U1.23 (D2), U2.55 (AD2)
D27: J1.b23 (D27), J4.b23 (D27), U1.25 (D3), U2.56 (AD3)
D28: J1.c23 (D28), J4.c23 (D28), U1.26 (D4), U2.5 (AD4)
D29: J1.a24 (D29), J4.a24 (D29), U1.27 (D5), U2.6 (AD5)
D30: J1.b24 (D30), J4.b24 (D30), U1.28 (D6), U2.7 (AD6)
D31: J1.c24 (D31), J4.c24 (D31), U1.29 (D7), U2.8 (AD7)
Earth: C20.2, FB1.2, J2.3, J2.6
GND: C1.2, C2.1, C3.2, C4.2, C5.2, C6.1, C7.2, C8.2, C10.2, C11.2, C13.1, C14.2, C15.2, C16.2, C17.2, C18.2, C19.2, C21.2, C22.2, C23.2, FB1.1, J1.a39 (GND), J1.b2 (GND), J1.b16 (GND), J1.b22 (GND), J1.b28 (GND), J1.b34 (GND), J1.b39 (GND), J1.c39 (GND), J3.6, J4.a39 (GND), J4.b2 (GND), J4.b16 (GND), J4.b22 (GND), J4.b28 (GND), J4.b34 (GND), J4.b39 (GND), J4.c39 (GND), JP1.2 (B), JP2.2 (B), R1.2, R3.1, U1.6 (NC), U1.9 (NC), U1.10 (A16), U1.24 (GND), U1.30 (CE), U2.1 (VSSOSC), U2.18 (PSPCFG3), U2.23 (VSSPLL), U2.24 (VSSRX), U2.29 (VSSTX), U2.32 (VSSTX), U2.45 (A14/PSPCFG1), U2.46 (VSS), U2.62 (VSS), U3.2 (GND), U4.4 (GND), U4.16 (GND), U4.24 (GND), U4.36 (GND), U5.1 (GND), Y1.2, Y1.4
unnamed: C20.1, R8.2, R9.2
unnamed: TP6.1, U4.34 (I/O)
unnamed: C5.1, R2.1, R4.2, TR1.7 (C_RD)
unnamed: R9.1, TR1.10 (C_RX)
unnamed: C16.1, R6.2, TR1.2 (C_TD)
unnamed: R8.1, TR1.15 (C_TX)
unnamed: C3.1, U2.3 (OSC1), Y1.3
unnamed: C4.1, U2.2 (OSC2), Y1.1
unnamed: R1.1, U2.16 (RBIAS)
unnamed: C10.1, U2.63 (VCAP)
R/~W: J1.c8 (R/~W), J4.c8 (R/~W), U2.51 (SI/RD/R~W), U4.28 (I/O)
SIZ0: J1.b9 (SIZ0), J4.b9 (SIZ0), U4.25 (I/O)
SIZ1: J1.a9 (SIZ1), J4.a9 (SIZ1), U4.27 (I/O)
~AS: J1.c9 (~AS), J4.c9 (~AS), U4.23 (I/O)
~DSACK0: J1.b8 (~DSACK0), J4.b8 (~DSACK0), U4.30 (I/O)
~DSACK1: J1.a8 (~DSACK1), J4.a8 (~DSACK1), U4.31 (I/O)
~DS: J1.b6 (~DS), J4.b6 (~DS), U4.33 (I/O)
~IRQ1: J1.c4 (~IRQ1), J4.c4 (~IRQ1), U4.44 (I/O)
~IRQ2: J1.b4 (~IRQ2), J4.b4 (~IRQ2), U4.43 (I/O)
~IRQ3: J1.a4 (~IRQ3), J4.a4 (~IRQ3), U4.42 (I/O)
~NUBUS: J1.c2 (~NUBUS), J4.c2 (~NUBUS)
~RESET: J1.a12 (~RESET), J4.a12 (~RESET), U4.39 (I/GCLR)

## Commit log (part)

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2023-11-11 rev0 boards
2023-11-11 firmware
2023-11-11 SE: fiddle some track positions for better fills
2023-11-11 First pass at driver
2023-11-13 Rearrange resources a bit
2023-11-13 add showDrivers utility
2023-11-13 Schematic PDFs
2023-11-13 readme
2023-11-14 Use correct address for SE board
2023-11-14 Try to explain some stuff a bit better
2023-11-14 CMake-ify declrom build
2023-11-14 Remove inadvertently included files
2023-11-14 Add build script, info on tools
2023-11-14 Ignore kicad project backups
2023-11-17 rev0 errata and bodges. I dun goofed.
2023-11-17 SE30 rev1
2023-11-27 bump DSACK delay to 8 cycles for safety
2023-11-28 Suppress byte-selects when ENC624J600 is unselected
2023-11-28 enforce some line-ending sanity
2023-11-28 driver WIP
2023-11-28 declrom source extension has to be uppercase .S
2023-11-29 remove old Makefile remnant
2023-11-29 rename declrom image to match PLD files
2023-11-30 Move shared code and headers into libraries
2023-11-30 add memory test tool
2023-11-30 fix compiler warnings
2023-11-30 Better notes on slot addresses
2023-12-05 Add spurious-interrupt errata
2023-12-05 Big ol' mess of updates
2023-12-05 Update to PLD readme - mention IIfx support
2023-12-06 Move errata to issue tracker
2023-12-06 move bytewise memcpy into enc624j600 lib
2023-12-06 Print address of globals at driver open breakpoint
2023-12-06 Comment clarifications
2023-12-06 Make registers volatile
2023-12-06 Remove unused debug string buffers
2023-12-06 rewrite rxbuf read routine for clarity
2023-12-08 Enable MacsBug stuff only for debug builds
2023-12-08 rewrite ReadPacket/ReadRest
2023-12-08 Add notes on relocation
2023-12-09 Add code annotations to GCC's asm output
2023-12-09 Fix incorrect transmit length calculation
2023-12-09 Keep track of link state, don't try to transmit with no link
2023-12-09 Make SE asm routines slightly less hideous
2023-12-09 discard padding for 802.2 Type 1 frames on receive
2023-12-09 Make protocol handler trampoline less weird
2023-12-09 Make register field mask/shift definitions consistent
2023-12-11 stop using #pragma parameter tricks, be more consistent with types
2023-12-11 More debug stuff
2023-12-11 Rewrite ReadPacket (take 2)
2023-12-11 Explicitly save A5 on protocol handler call
2023-12-11 Tidy up packet length calculations
2023-12-11 Count TX errors as TX errors
2023-12-11 Get rid of PC-relative references
2023-12-11 More debug messages
2023-12-12 Use a single debug-string buffer
2023-12-12 Reset chip on shutdown
    Mitigation for issue #4.
2023-12-12 debugging improvements
2023-12-12 Add git info to version strings
2023-12-12 general code tidyup
2023-12-12 Make SWAPBYTES macro explicitly byte-width
    In some cases it was optimizing away to nothing otherwise. Never trust a compiler.
2023-12-12 Disable async transmit for now
2023-12-12 use regular memcpy for chip reads
2023-12-12 cancel transmit if we end up stomping on an in-progress transmit
2023-12-12 use enc624j600 library for pointer calculation
2023-12-12 better explanation for a5-save workaround
2023-12-13 Fix address-calculation bug
2023-12-13 Refactor a bunch of stuff
    - Make a bunch of function arguments const
    - Tidy up comments
    - Replace ad-hoc receive header processing with struct
2023-12-13 Fix incorrect offset for csCode
2023-12-13 Add macsbug labels and better comments to header
2023-12-13 Improved macsbug symbol macro
2023-12-15 Make shutdown hook a bit less unwieldy
2023-12-15 Better coverage for ISR edge/error cases
2023-12-15 Clarify some comments
2023-12-15 Get async transmit working
    - Preserve extra registers across IODone call
    - Acknowledge transmit interrupt *before* calling IODone
2023-12-16 Compiler option tweaks for debug build
2023-12-16 Use registers for argument passing in a few places
    - Driver entrypoints, since this avoids having to convert between Apple
    and C ABI
    - enc624j600_read_rxbuf, since this is on the critical path in the
    ReadPacket/ReadRest callback
2023-12-16 Use memcpy for buffer reads
    The back-to-back access restricions imposed by issue #3 only apply to
    writes, for reads we can go as fast as we want.
2023-12-16 inline critical-path enc624j600 functions
2023-12-17 Rework ISR wrappers for SE support
2023-12-17 don't do VM stuff on SE
2023-12-17 Better hardware detection and error handling
    - Use user-data pointer register to positively identify that an
    ENC624J600 is present where we think it is
    - Check for and handle more errors during startup
    - Check for Gestalt and SlotManger traps before using them
    - Only try to start SE driver if running on an SE
2023-12-17 Correct addresses of memory-access registers
2023-12-17 Add memory test
2023-12-17 Use system-provided icons
    Turns out that the system already gives 'comd' files the appropriate
    icon if their creator code is 'Enet'. Do this instead of trying and
    failing to bring our own icon.
    Fixes issue #9
2023-12-18 SE: Inhibit byte strobes when not selected
    Bring into line with the SE/30 glue logic
2023-12-18 Add git version info to ROM
2023-12-18 Driver build requires Universal Interfaces
2023-12-18 Generate C-header version of ROM image
2023-12-20 fix incorrect sResource ID
2023-12-20 Redo flags with struct bitfields
2023-12-20 Move packet header into separate struct for clarity
2023-12-20 Replace load-time debug break with 'panic button'
2023-12-21 Fix off-by-one error in read wraparound
2023-12-24 Pass userISR() argument in A0
    DeferUserFn() passes the function argument in A0, so we need to match
    this, otherwise we'll crash under Virtual Memory
2023-12-24 Fix typo in MIIRD register name
2023-12-24 set MIIRD command bit for PHY-register reads
2023-12-24 Check device-ID bits as art of device detection
2023-12-25 Process completions in a deferred task
    This avoids a possible deadlock situation when ill-behaved software
    tries to do blocking IO in a completion routine.
2023-12-25 Remove shutdown hook if driver gets closed
2023-12-25 Increase reset delay to 1.5 seconds
    Big-hammer workaround for issue #20
2023-12-25 Preload deferred task fields
2023-12-25 Project status update
2023-12-25 Move debug panic-button break to after relocation
2023-12-27 Add timestamp to debug log entries
2023-12-27 Get rid of deferred-task IO completion hack
    It introduced bugs in other situations (due to out-of-order IODone()
    calls), and the deadlock issue I was attempting to solve with it turns
    out to also be reproducible on other network cards, suggesting that it
    is likely being caused elsewhere in the system.
2023-12-27 Refactor utility functions
    Move debug_log into utils.c
    Move small hotspot functions into header for inlining
    Move used-in-one-place functions to point of use
    Use Toolbox Delay() function instead of rolling our own equivalent
2023-12-27 Use short ints where possible
    The 68000 is 16 bit internally, and 32 bit operations cause a
    performance hit.
2023-12-27 Make PHY regsiter reads work properly
2023-12-27 Record stats for unknown-protocol packets
2023-12-27 Get link speed and duplex info
2023-12-28 Fix missing include
2023-12-28 Deregister shutdown handler if driver open fails
2023-12-30 Fix issue with -O3 builds
    At -O3, gcc was optimizing the bytewise memory-copy loop required as a
    workaround for issue #3, into an inline memcpy() that used word writes.
2023-12-31 Use 'vers' resource format for version info
    This will allow the Installer to make correct decisions about updating
    (once we get an installer working)
2024-01-03 formatting and clarity fixes
2024-01-04 First pass at installer
2024-01-05 Remove DeRez annotations
2024-01-05 Add identifiers to installer resources
    Define names (on a reverse-engineered best-guess basis) to identify
    installer script resources. Remove some 'dead' rules and assertions that
    pertain only to A/UX and TokenTalk.
2024-01-06 More installer reverse engineering
2024-01-16 Use board_defs for resource board ID
2024-01-16 make installer build script more user-friendly
2024-01-17 Branch optimizations
    - Give branch-prediction hints on 'hot' paths
    - Use 'Jxx' branch instructions to make the assembler use the smallest
    possible branch offset
2024-01-17 ReadPacket optimizations
    - Remove redundant error checks
    - Remove redundant return value from enc624j600_read_rxbuf
2024-01-17 Installer: add package for SE driver
2024-01-19 SE: delay data strobes by one GAL delay
2024-01-19 Build processor-specific version of enc624j600 lib
2024-01-19 Fix embarrassing pointer bug in SE ISR
2024-01-19 Be truthful with the compiler about alignment tricks
    In the interest of performance, we copy and compare 6-byte ethernet
    hardware addresses as a 4-byte `unsigned long` and a 2-byte `unsigned
    short`. But the 68000 can only operate on those types when they are
    aligned at on word boundaries, and throws an Address Error otherwise.
    Instead of describing hardware addresses as just an array of bytes and
    casting pointers willy nilly, describe them as a `union` of a byte array
2024-01-28 Rev1 hardware
2024-02-17 Rev1 PLDs
2024-02-17 SPISEL pulldown resistor should be 100K, not 10K
2024-02-17 Suppress meaningless linking error
2024-02-17 Cleanup driver comments
2024-02-17 Assorted driver performance tweaks
    - Add branch annotations
    - Be less fussy about multicast address matching
    - Move SE vs. SE/30 conditional to compile time
2024-02-17 Return old EIE value when disabling interrupts
2024-02-17 Optimize protocol-handler table routines
2024-02-17 Remove workaround for issue #3
    Rev1 hardware is done with a hardware fix for
    Issue #3. This significantly increases write
    performance, at the cost of breaking compatibility
    with rev0 hardware.
    Since only one set of rev0 boards was ever built,
    and they're mine, I think this is OK :)
2024-02-17 Bump version to 1.0.0 beta 1
2024-02-17 SE30 CPLD: enable JTAG pullups
2024-02-18 update schematics
2024-02-18 Add licenses
2024-02-19 SE30: Remove delay buffer on /BxSEL lines
2024-02-24 Mitigation for DSACK rise time issues
    In machines with multiple expansion cards, the additional parasitic capacitance
    on the DSACK lines may increase the signal rise time beyond acceptable limits,
    especially on accelerated systems. This may cause instability if a new bus
    cycle gets underway before DSACK has stabilised - such behavior was observed
    with an Interware 50MHz accelerator.
    As a mitigation for this, drive DSACK push-pull, and only tristate it when the
2024-03-04 SE30: add missing trace
2024-03-04 SE30: remove unused rom resource from declrom
2024-03-04 Add MacTCP to install disk
2024-03-05 add notes on expectations
2024-03-06 Fix installer breakage
2024-04-05 debug build: add extra messages for startup errors
2024-04-06 add macro for _Debugger trap
2024-04-06 Rewrite ringbuffer routines in assembly
    The previous routines to copy data from the receive ringbuffer were a
    mix of assembly and C. Rewrite as all assembly to reduce overhead in
    parameter passing.
2024-04-25 Breakout: use threaded inserts for mounting
    Resize mounting holes for use with Wurth 9774025360R threaded inserts.
2024-04-29 programROM: fix declrom probe behavior
    Probe routine was repeatedly probing slot+0xff0000 instead of probing
    the last 16 bytes of the slot as intended.
2024-04-29 Adjust terminology used with DSACK logic
    DSACK outputs are not strictly open-collector - adjust comments and
    term names to reflect this correction.
2024-07-24 Update software status to mention A/UX driver
2024-11-25 Remove unused register debugging code
    Never fully implemented it, never ended up writing any tools to use it,
    don't really need it now that the driver is working.
2024-11-25 Tidy up debugging functions
    - Wrap the sprintf()-DebugStr() pattern into a single DebugPrintf() call
    - DBGP() and DBGS() macros to call DebugPrintf() and DebugStr() in debug
    builds
2024-11-26 They call it cmake because it makes you want to walk into the sea
